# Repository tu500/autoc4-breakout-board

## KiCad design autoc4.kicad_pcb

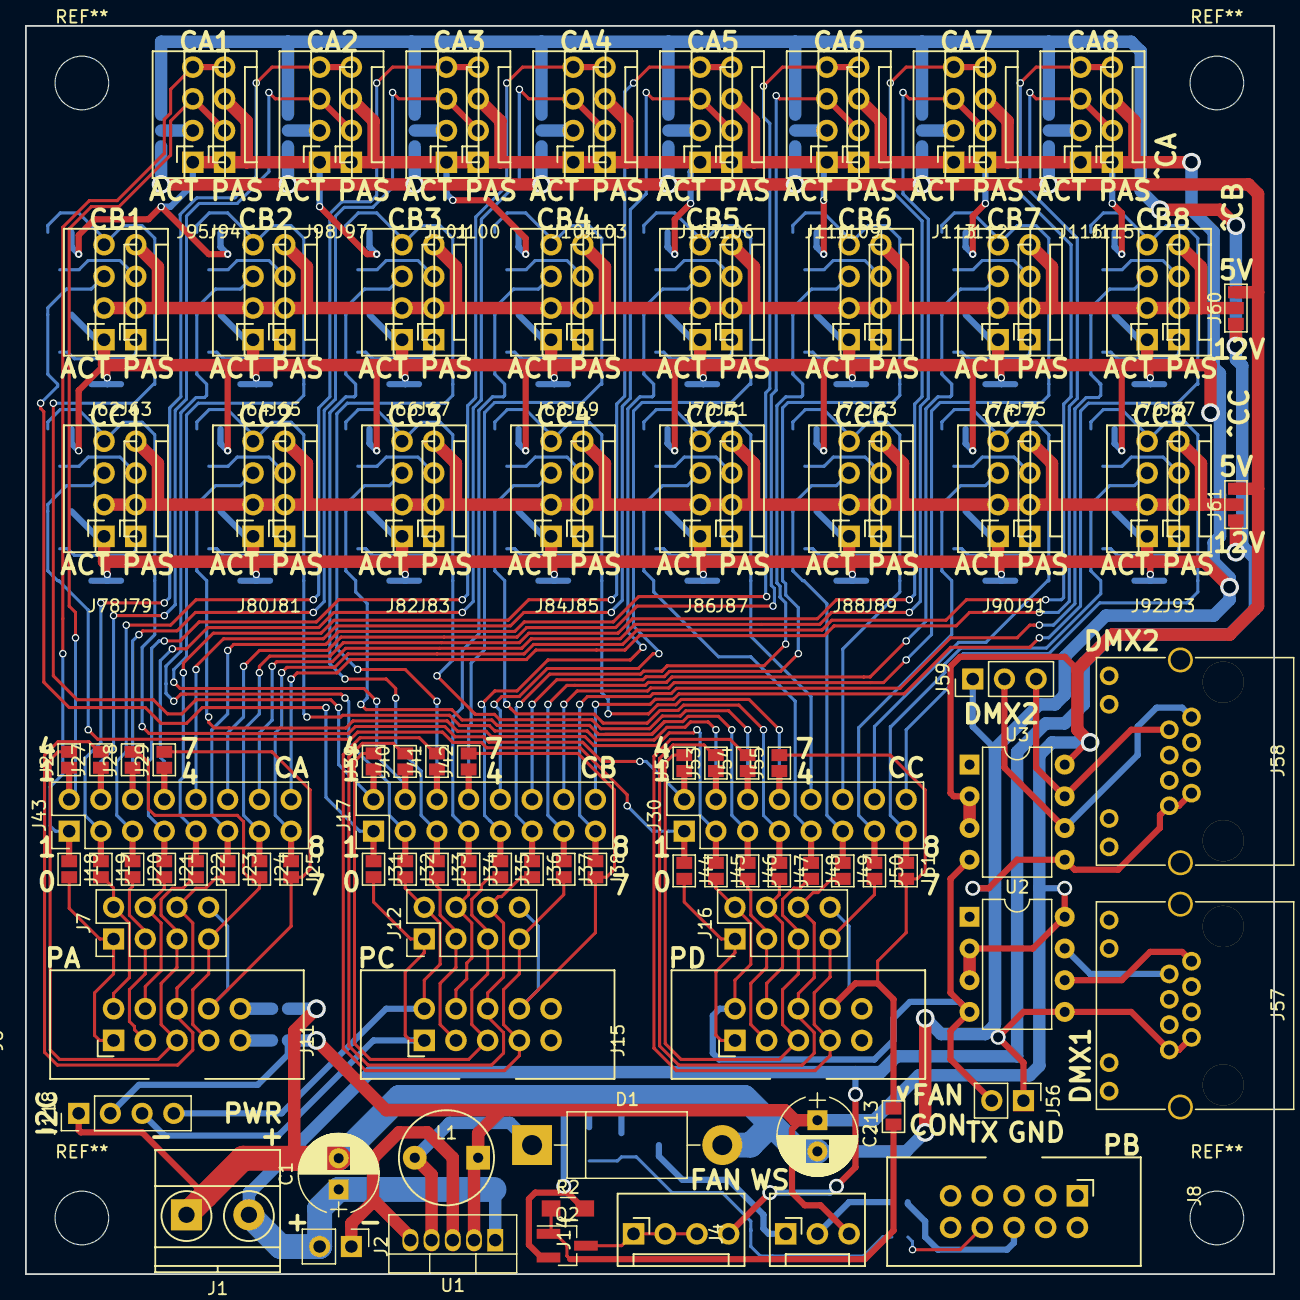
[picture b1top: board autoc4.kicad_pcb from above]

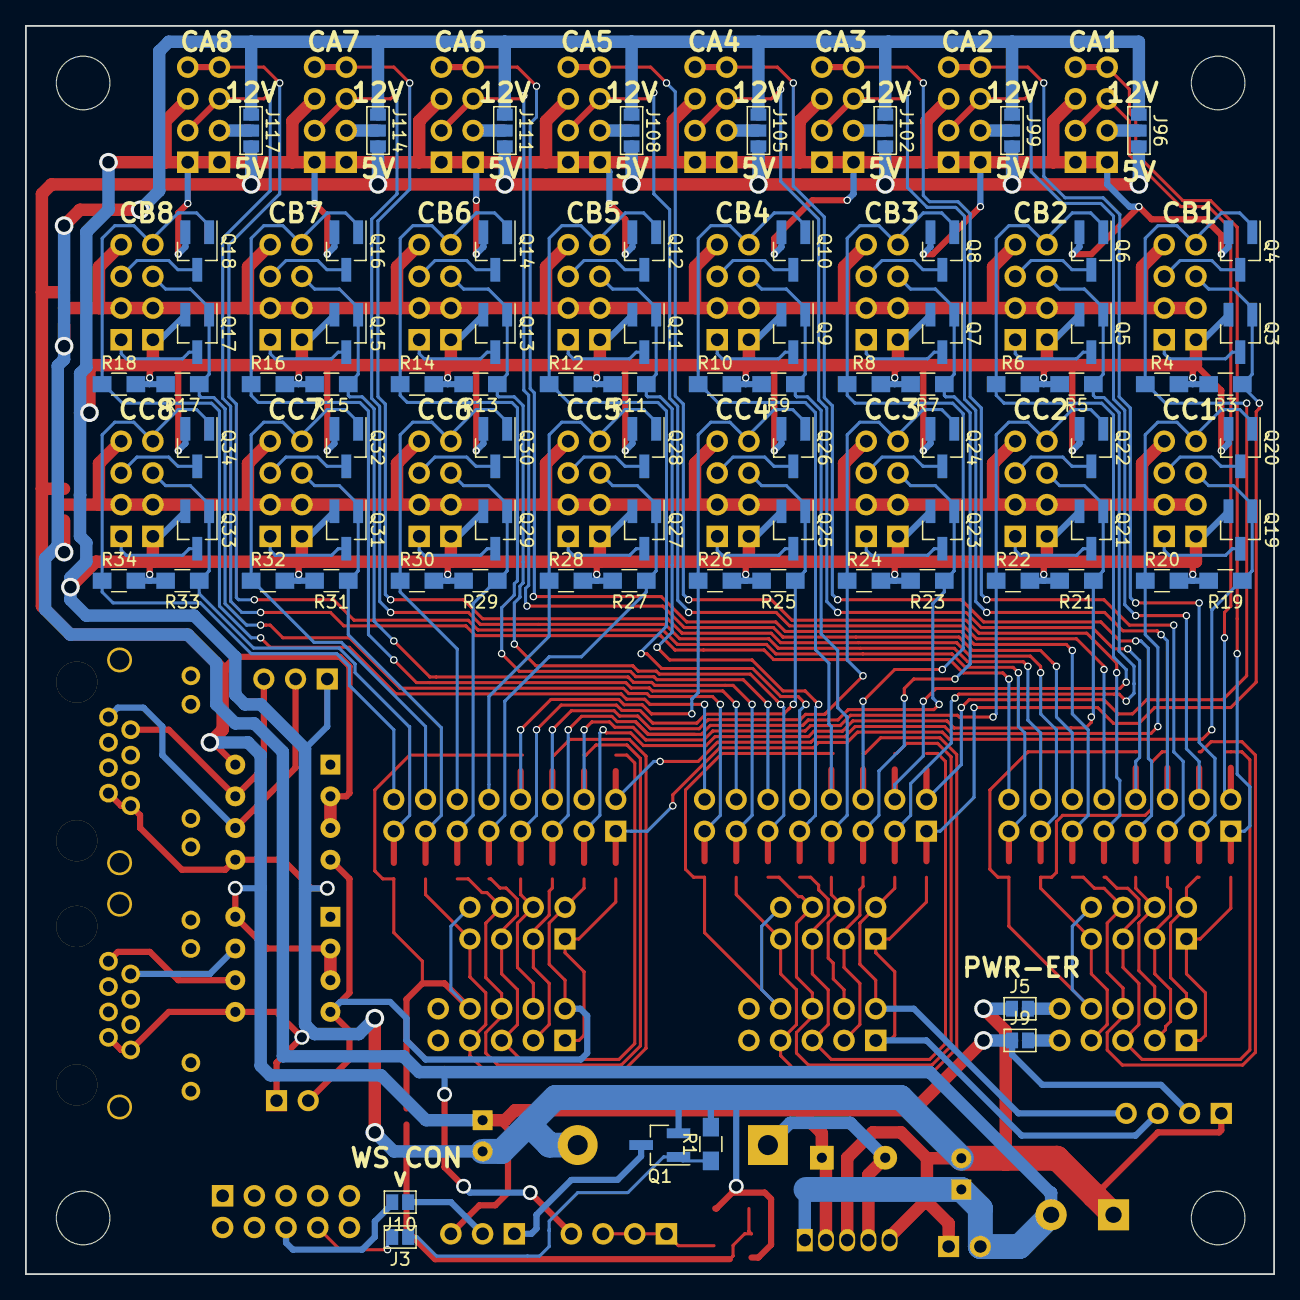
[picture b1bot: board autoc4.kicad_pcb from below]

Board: 2 copper layers, 100.0 x 100.0 mm, 193 parts (78 on the bottom side), 131 nets.

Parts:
C1: 100uF; CP_Radial_D6.3mm_P2.50mm
C2: 330uF; CP_Radial_D6.3mm_P2.50mm
D1: DO201AD; D_DO-201AD_P15.24mm_Horizontal
J1: Screw_Terminal_1x02; TerminalBlock_Pheonix_MKDS1.5-2pol
J2, J56: CONN_01X02; Pin_Header_Straight_1x02_Pitch2.54mm
J3, J5, J9, J10, J13, J18, J19, J20, J21, J22, J23, J24, J25, J26, J27, J28, J29, J31, J32, J33, J34, J35, J36, J37, J38, J39, J40, J41, J42, J44, J45, J46, J47, J48, J49, J50, J51, J52, J53, J54, J55: GS2
J4: CONN_01X03; PSG_Straight_03
J6, J8, J11, J15: CONN_02X05; Pin_Header_Boxed_Straight_2x05
J7, J12, J16: CONN_02X04; Pin_Header_Straight_2x04_Pitch2.54mm
J14, J62, J63, J64, J65, J66, J67, J68, J69, J70, J71, J72, J73, J74, J75, J76, J77, J78, J79, J80, J81, J82, J83, J84, J85, J86, J87, J88, J89, J90, J91, J92, J93, J94, J95, J97, J98, J100, J101, J103, J104, J106, J107, J109, J110, J112, J113, J115, J116: CONN_01X04; PSG_Straight_04
J17, J30, J43: CONN_02X08; Pin_Header_Straight_2x08_Pitch2.54mm
J57, J58: RJ45_LEDS; RJHSE538X
J59: CONN_01X03; Pin_Header_Straight_1x03_Pitch2.54mm
J60, J61, J96, J99, J102, J105, J108, J111, J114, J117: GS3
J118: CONN_01X04; Pin_Header_Straight_1x04_Pitch2.54mm
L1: 330uH; INDUCTOR_V
Q1, Q2, Q3, Q4, Q5, Q6, Q7, Q8, Q9, Q10, Q11, Q12, Q13, Q14, Q15, Q16, Q17, Q18, Q19, Q20, Q21, Q22, Q23, Q24, Q25, Q26, Q27, Q28, Q29, Q30, Q31, Q32, Q33, Q34: AO3400A; SOT-23_Handsoldering
R1, R2: R; R_0805_HandSoldering
R3, R4, R5, R6, R7, R8, R9, R10, R11, R12, R13, R14, R15, R16, R17, R18, R19, R20, R21, R22, R23, R24, R25, R26, R27, R28, R29, R30, R31, R32, R33, R34: 100k; R_0805_HandSoldering
U1: LM2575-5.0; TO-220-5_Pentawatt_Multiwatt-5_Vertical
U2, U3: SN75176BP; DIP-8_W7.62mm

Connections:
+5V: C2.1, J4.3, J9.1, J60.1, J61.1, J96.1, J99.1, J102.1, J105.1, J108.1, J111.1, J114.1, J117.1, J118.2, L1.1, U1.2, U2.2, U2.3, U2.8, U3.2, U3.3, U3.8
+12V: C1.1, J1.2, J2.2, J14.4, J60.3, J61.3, J96.3, J99.3, J102.3, J105.3, J108.3, J111.3, J114.3, J117.3, U1.1
/CA1_1: J18.1, J43.1, J94.4, J95.4
/CA1_2: J19.1, J43.3, J97.4, J98.4
/CA1_3: J20.1, J43.5, J100.4, J101.4
/CA1_4: J21.1, J43.7, J103.4, J104.4
/CA1_5: J22.1, J43.9, J106.4, J107.4
/CA1_6: J23.1, J43.11, J109.4, J110.4
/CA1_7: J24.1, J43.13, J112.4, J113.4
/CA1_8: J25.1, J43.15, J115.4, J116.4
/CA2_1: J26.1, J43.2, J94.2, J95.3
/CA2_2: J27.1, J43.4, J97.2, J98.3
/CA2_3: J28.1, J43.6, J100.2, J101.3
/CA2_4: J29.1, J43.8, J103.2, J104.3
/CA2_5: J43.10, J106.2, J107.3
/CA2_6: J43.12, J109.2, J110.3
/CA2_7: J43.14, J112.2, J113.3
/CA2_8: J43.16, J115.2, J116.3
/CB1/VCC: J60.2, J62.2, J63.2, J63.4, J64.2, J65.2, J65.4, J66.2, J67.2, J67.4, J68.2, J69.2, J69.4, J70.2, J71.2, J71.4, J72.2, J73.2, J73.4, J74.2, J75.2, J75.4, J76.2, J77.2, J77.4
/CB1_1: J17.1, J31.1, J62.3, Q3.1, R3.1
/CB1_2: J17.3, J32.1, J64.3, Q5.1, R5.1
/CB1_3: J17.5, J33.1, J66.3, Q7.1, R7.1
/CB1_4: J17.7, J34.1, J68.3, Q9.1, R9.1
/CB1_5: J17.9, J35.1, J70.3, Q11.1, R11.1
/CB1_6: J17.11, J36.1, J72.3, Q13.1, R13.1
/CB1_7: J17.13, J37.1, J74.3, Q15.1, R15.1
/CB1_8: J17.15, J38.1, J76.3, Q17.1, R17.1
/CB2_1: J17.2, J39.1, J62.4, Q4.1, R4.1
/CB2_2: J17.4, J40.1, J64.4, Q6.1, R6.1
/CB2_3: J17.6, J41.1, J66.4, Q8.1, R8.1
/CB2_4: J17.8, J42.1, J68.4, Q10.1, R10.1
/CB2_5: J17.10, J70.4, Q12.1, R12.1
/CB2_6: J17.12, J72.4, Q14.1, R14.1
/CB2_7: J17.14, J74.4, Q16.1, R16.1
/CB2_8: J17.16, J76.4, Q18.1, R18.1
/CC1/VCC: J61.2, J78.2, J79.2, J79.4, J80.2, J81.2, J81.4, J82.2, J83.2, J83.4, J84.2, J85.2, J85.4, J86.2, J87.2, J87.4, J88.2, J89.2, J89.4, J90.2, J91.2, J91.4, J92.2, J93.2, J93.4
/CC1_1: J30.1, J44.1, J78.3, Q19.1, R19.1
/CC1_2: J30.3, J45.1, J80.3, Q21.1, R21.1
/CC1_3: J30.5, J46.1, J82.3, Q23.1, R23.1
/CC1_4: J30.7, J47.1, J84.3, Q25.1, R25.1
/CC1_5: J30.9, J48.1, J86.3, Q27.1, R27.1
/CC1_6: J30.11, J49.1, J88.3, Q29.1, R29.1
/CC1_7: J30.13, J50.1, J90.3, Q31.1, R31.1
/CC1_8: J30.15, J51.1, J92.3, Q33.1, R33.1
/CC2_1: J30.2, J52.1, J78.4, Q20.1, R20.1
/CC2_2: J30.4, J53.1, J80.4, Q22.1, R22.1
/CC2_3: J30.6, J54.1, J82.4, Q24.1, R24.1
/CC2_4: J30.8, J55.1, J84.4, Q26.1, R26.1
/CC2_5: J30.10, J86.4, Q28.1, R28.1
/CC2_6: J30.12, J88.4, Q30.1, R30.1
/CC2_7: J30.14, J90.4, Q32.1, R32.1
/CC2_8: J30.16, J92.4, Q34.1, R34.1
/FAN_CTL: J13.1, Q2.1, R2.1
/PA0: J6.1, J7.1, J18.2
/PA1: J6.2, J7.2, J19.2
/PA2: J6.3, J7.3, J20.2
/PA3: J6.4, J7.4, J21.2
/PA4: J6.5, J7.5, J22.2, J26.2
/PA5: J6.6, J7.6, J23.2, J27.2
/PA6: J6.7, J7.7, J24.2, J28.2
/PA7: J6.8, J7.8, J25.2, J29.2
/PB0: J3.2, J8.8
/PB1: J8.6, J10.2
/PC0: J11.1, J12.1, J31.2, J118.3
/PC1: J11.2, J12.2, J32.2, J118.4
/PC2: J11.3, J12.3, J33.2
/PC3: J11.4, J12.4, J34.2
/PC4: J11.5, J12.5, J35.2, J39.2
/PC5: J11.6, J12.6, J36.2, J40.2
/PC6: J11.7, J12.7, J37.2, J41.2
/PC7: J11.8, J12.8, J38.2, J42.2
/PD0: J15.1, J16.1, J44.2
/PD1: J15.2, J16.2, J45.2, J56.2, U2.4, U3.4
/PD2: J15.3, J16.3, J46.2
/PD3: J15.4, J16.4, J47.2
/PD4: J15.5, J16.5, J48.2, J52.2
/PD5: J15.6, J16.6, J49.2, J53.2
/PD6: J15.7, J16.7, J50.2, J54.2
/PD7: J13.2, J15.8, J16.8, J51.2, J55.2
/WS_POWER: J3.1, Q1.1, R1.1
/WS_STATUS: J4.2, J10.1
GND: C1.2, C2.2, D1.2, J1.1, J2.1, J5.1, J56.1, J57.7, J57.8, J58.7, J58.8, J59.1, J62.1, J64.1, J66.1, J68.1, J70.1, J72.1, J74.1, J76.1, J78.1, J80.1, J82.1, J84.1, J86.1, J88.1, J90.1, J92.1, J94.1, J94.3, J95.1, J97.1, J97.3, J98.1, J100.1, J100.3, J101.1, J103.1, J103.3, J104.1, J106.1, J106.3, J107.1, J109.1, J109.3, J110.1, J112.1, J112.3, J113.1, J115.1, J115.3, J116.1, J118.1, Q1.2, Q2.2, Q3.2, Q4.2, Q5.2, Q6.2, Q7.2, Q8.2, Q9.2, Q10.2, Q11.2, Q12.2, Q13.2, Q14.2, Q15.2, Q16.2, Q17.2, Q18.2, Q19.2, Q20.2, Q21.2, Q22.2, Q23.2, Q24.2, Q25.2, Q26.2, Q27.2, Q28.2, Q29.2, Q30.2, Q31.2, Q32.2, Q33.2, Q34.2, R1.2, R2.2, R3.2, R4.2, R5.2, R6.2, R7.2, R8.2, R9.2, R10.2, R11.2, R12.2, R13.2, R14.2, R15.2, R16.2, R17.2, R18.2, R19.2, R20.2, R21.2, R22.2, R23.2, R24.2, R25.2, R26.2, R27.2, R28.2, R29.2, R30.2, R31.2, R32.2, R33.2, R34.2, U1.3, U1.5, U2.5, U3.5
unnamed: D1.1, L1.2, U1.4
unnamed: J4.1, Q1.3
unnamed: J5.2, J6.10
unnamed: J6.9, J9.2
unnamed: J14.1, J14.2, J14.3, Q2.3
unnamed: J57.1, U2.6
unnamed: J57.2, U2.7
unnamed: J58.1, J59.2, U3.6
unnamed: J58.2, J59.3, U3.7
unnamed: J63.1, Q3.3
unnamed: J63.3, Q4.3
unnamed: J65.1, Q5.3
unnamed: J65.3, Q6.3
unnamed: J67.1, Q7.3
unnamed: J67.3, Q8.3
unnamed: J69.1, Q9.3
unnamed: J69.3, Q10.3
unnamed: J71.1, Q11.3
unnamed: J71.3, Q12.3
unnamed: J73.1, Q13.3
unnamed: J73.3, Q14.3
unnamed: J75.1, Q15.3
unnamed: J75.3, Q16.3
unnamed: J77.1, Q17.3
unnamed: J77.3, Q18.3
unnamed: J79.1, Q19.3
unnamed: J79.3, Q20.3
unnamed: J81.1, Q21.3
unnamed: J81.3, Q22.3
unnamed: J83.1, Q23.3
unnamed: J83.3, Q24.3
unnamed: J85.1, Q25.3
unnamed: J85.3, Q26.3
unnamed: J87.1, Q27.3
unnamed: J87.3, Q28.3
unnamed: J89.1, Q29.3
unnamed: J89.3, Q30.3
unnamed: J91.1, Q31.3
unnamed: J91.3, Q32.3
unnamed: J93.1, Q33.3
unnamed: J93.3, Q34.3
unnamed: J95.2, J96.2
unnamed: J98.2, J99.2
unnamed: J101.2, J102.2
unnamed: J104.2, J105.2
unnamed: J107.2, J108.2
unnamed: J110.2, J111.2
unnamed: J113.2, J114.2
unnamed: J116.2, J117.2

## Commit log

2017-06-24 Add bug notes
